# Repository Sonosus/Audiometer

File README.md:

# Audiometer
Simple VU style level meter board.
Untested, I can't verify that this won't blow up!
Made using Stretch, a plugin for KiCAD that lets users edit PCB files in Inkscape.

Shield: [![CC BY-SA 4.0][cc-by-sa-shield]][cc-by-sa]

This work is licensed under a
[Creative Commons Attribution-ShareAlike 4.0 International License][cc-by-sa].

[![CC BY-SA 4.0][cc-by-sa-image]][cc-by-sa]

[cc-by-sa]: http://creativecommons.org/licenses/by-sa/4.0/
[cc-by-sa-image]: https://licensebuttons.net/l/by-sa/4.0/88x31.png
[cc-by-sa-shield]: https://img.shields.io/badge/License-CC%20BY--SA%204.0-lightgrey.svg

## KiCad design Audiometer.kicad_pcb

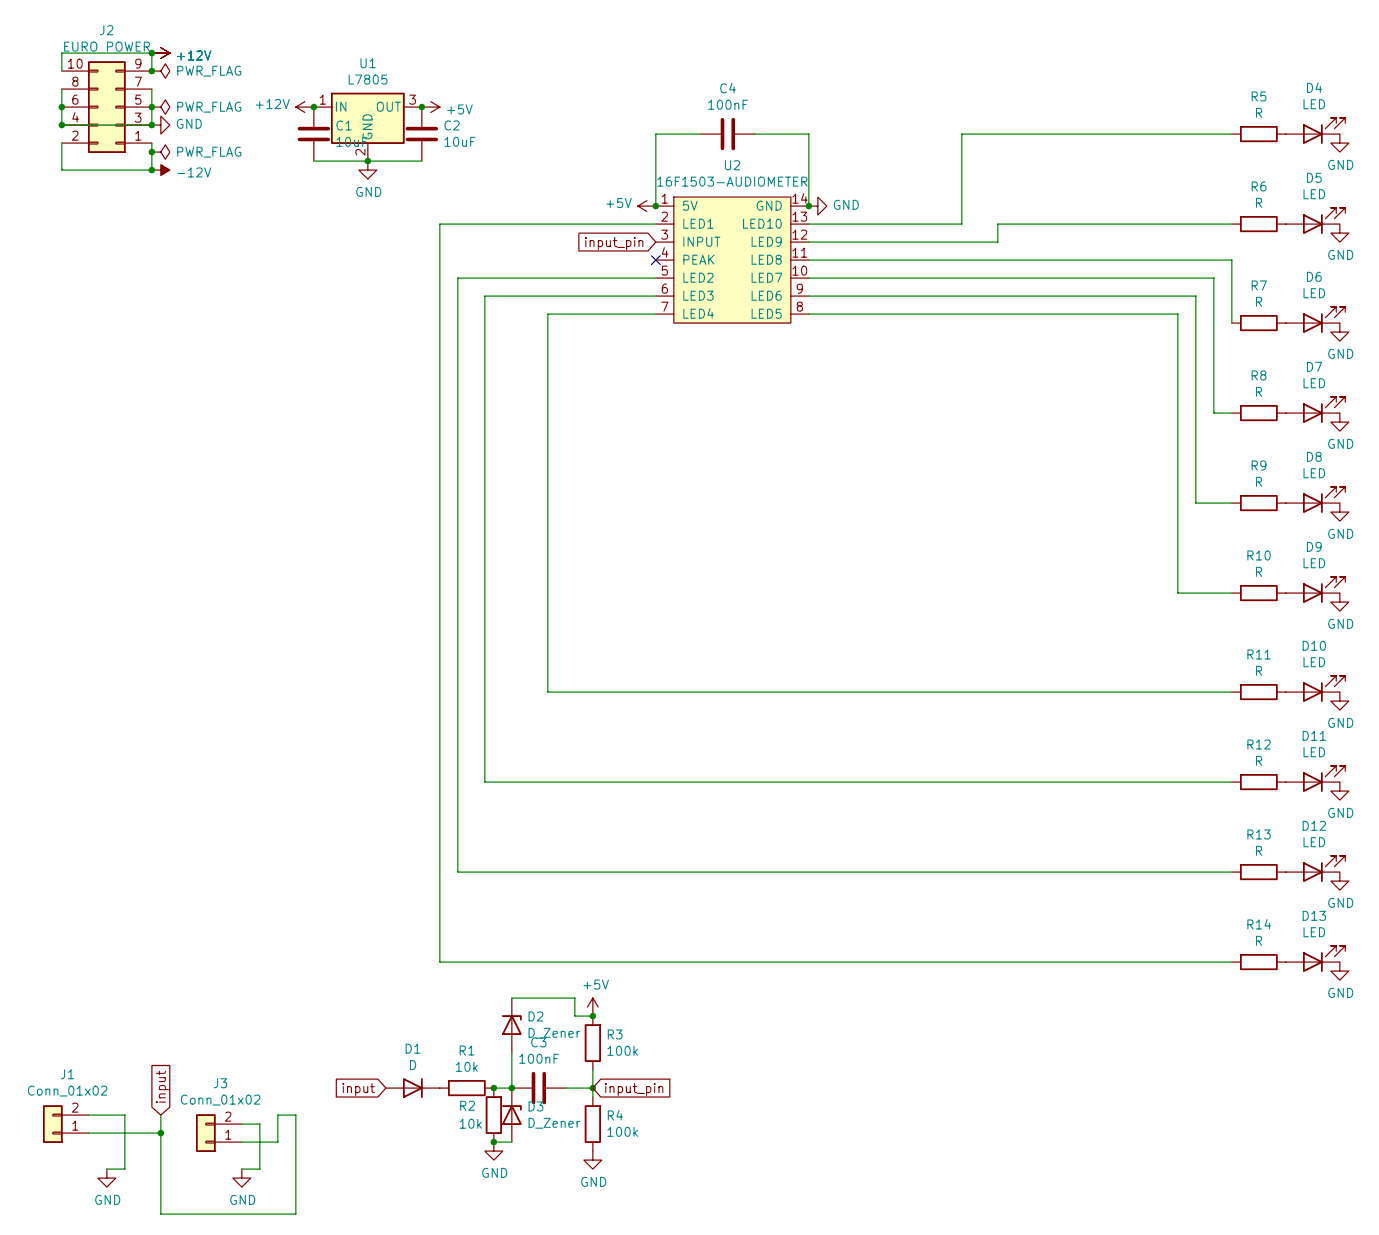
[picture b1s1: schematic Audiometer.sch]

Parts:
C1, C2: 10uF; CP_Radial_D6.3mm_P2.50mm
C3, C4: 100nF; C_Disc_D6.0mm_W4.4mm_P5.00mm
D1: D; D_DO-35_SOD27_P7.62mm_Horizontal
D2, D3: D_Zener; D_DO-35_SOD27_P7.62mm_Horizontal
D4, D5, D6, D7, D8, D9, D10, D11, D12, D13: LED; LED_D5.0mm
J1, J3: Conn_01x02; PinHeader_1x02_P2.54mm_Vertical
J2: EURO POWER; Power_Header
R1, R2: 10k; R_Axial_DIN0207_L6.3mm_D2.5mm_P10.16mm_Horizontal
R3, R4: 100k; R_Axial_DIN0207_L6.3mm_D2.5mm_P10.16mm_Horizontal
R5, R6, R7, R8, R9, R10, R11, R12, R13, R14: R; R_Axial_DIN0207_L6.3mm_D2.5mm_P10.16mm_Horizontal
U1: L7805; TO-220-3_Vertical
U2: 16F1503-AUDIOMETER; DIP-14_W7.62mm_Socket_LongPads

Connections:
+5V: C2.1, C4.2, D2.1 (K), R3.2, U1.3 (OUT), U2.1 (5V)
+12V: C1.1, J2.9, J2.10, U1.1 (IN)
-12V: J2.1, J2.2
GND: C1.2, C2.2, C4.1, D3.2 (A), D4.1 (K), D5.1 (K), D6.1 (K), D7.1 (K), D8.1 (K), D9.1 (K), D10.1 (K), D11.1 (K), D12.1 (K), D13.1 (K), J1.2, J2.3, J2.4, J2.5, J2.6, J2.7, J2.8, J3.2, R2.1, R4.1, U1.2 (GND), U2.14 (GND)
unnamed: C3.2, D2.2 (A), D3.1 (K), R1.1, R2.2
unnamed: D1.1 (K), R1.2
unnamed: D4.2 (A), R5.1
unnamed: D5.2 (A), R6.1
unnamed: D6.2 (A), R7.1
unnamed: D7.2 (A), R8.1
unnamed: D8.2 (A), R9.1
unnamed: D9.2 (A), R10.1
unnamed: D10.2 (A), R11.1
unnamed: D11.2 (A), R12.1
unnamed: D12.2 (A), R13.1
unnamed: D13.2 (A), R14.1
unnamed: R5.2, U2.13 (LED10)
unnamed: R6.2, U2.12 (LED9)
unnamed: R7.2, U2.11 (LED8)
unnamed: R8.2, U2.10 (LED7)
unnamed: R9.2, U2.9 (LED6)
unnamed: R10.2, U2.8 (LED5)
unnamed: R11.2, U2.7 (LED4)
unnamed: R12.2, U2.6 (LED3)
unnamed: R13.2, U2.5 (LED2)
unnamed: R14.2, U2.2 (LED1)
input: D1.2 (A), J1.1, J3.1
input_pin: C3.1, R3.1, R4.2, U2.3 (INPUT)

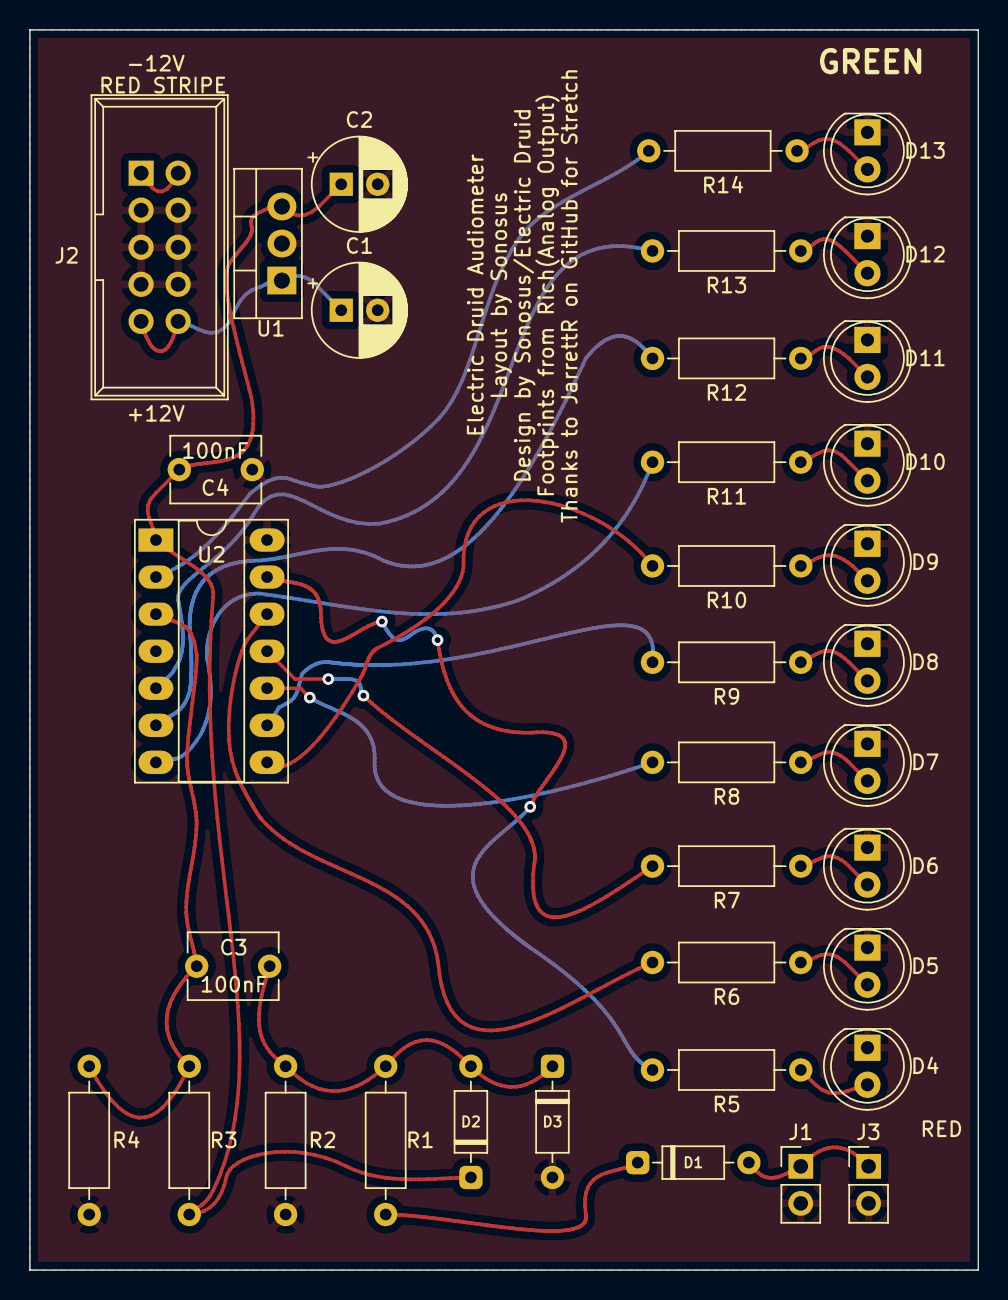
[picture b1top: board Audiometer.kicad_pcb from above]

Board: 2 copper layers, 65.0 x 85.0 mm, 36 parts (0 on the bottom side), 28 nets.

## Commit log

2021-05-23 Initial upload
2021-05-23 Update Readme to include info
2021-05-23 Add CC licensing docs
2021-05-23 Add docs
2021-05-23 Add image to Readme
2021-05-24 [ImgBot] Optimize images
    /Docs/audiorender.png -- 242.40kb -> 198.65kb (18.05%)
